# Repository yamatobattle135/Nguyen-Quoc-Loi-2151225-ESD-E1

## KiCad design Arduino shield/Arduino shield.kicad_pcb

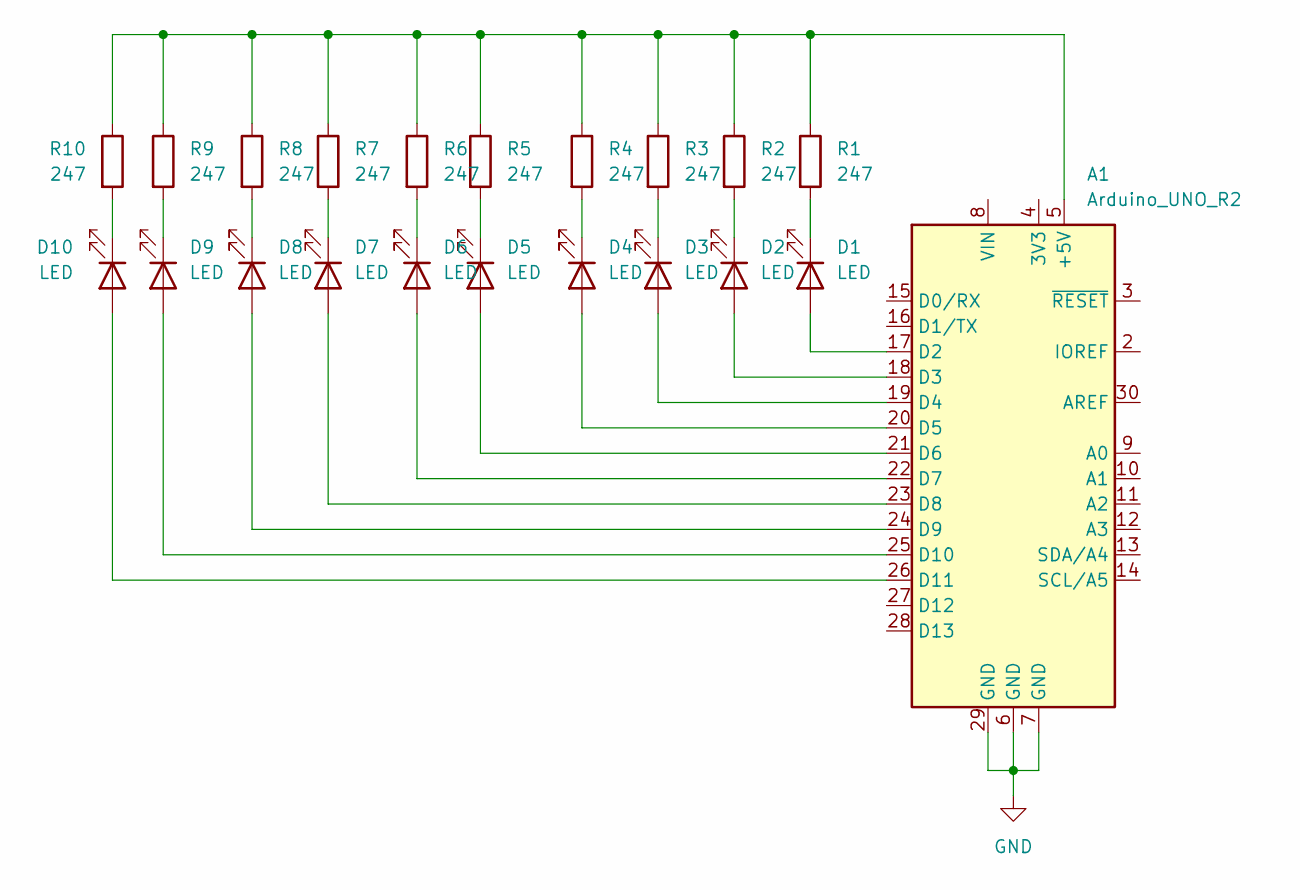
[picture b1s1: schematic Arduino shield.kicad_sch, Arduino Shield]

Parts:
A1: Arduino_UNO_R2
D1, D2, D3, D4, D5, D6, D7, D8, D9, D10: LED; LED_0805_2012Metric
R1, R2, R3, R4, R5, R6, R7, R8, R9, R10: 247; R_0805_2012Metric

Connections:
GND: A1.6 (GND), A1.7 (GND), A1.29 (GND)
unnamed: A1.5 (+5V), R1.1, R2.1, R3.1, R4.1, R5.1, R6.1, R7.1, R8.1, R9.1, R10.1
unnamed: A1.17 (D2), D1.2 (A)
unnamed: A1.18 (D3), D2.2 (A)
unnamed: A1.19 (D4), D3.2 (A)
unnamed: A1.20 (D5), D4.2 (A)
unnamed: A1.21 (D6), D5.2 (A)
unnamed: A1.22 (D7), D6.2 (A)
unnamed: A1.23 (D8), D7.2 (A)
unnamed: A1.24 (D9), D8.2 (A)
unnamed: A1.25 (D10), D9.2 (A)
unnamed: A1.26 (D11), D10.2 (A)
unnamed: D1.1 (K), R1.2
unnamed: D2.1 (K), R2.2
unnamed: D3.1 (K), R3.2
unnamed: D4.1 (K), R4.2
unnamed: D5.1 (K), R5.2
unnamed: D6.1 (K), R6.2
unnamed: D7.1 (K), R7.2
unnamed: D8.1 (K), R8.2
unnamed: D9.1 (K), R9.2
unnamed: D10.1 (K), R10.2

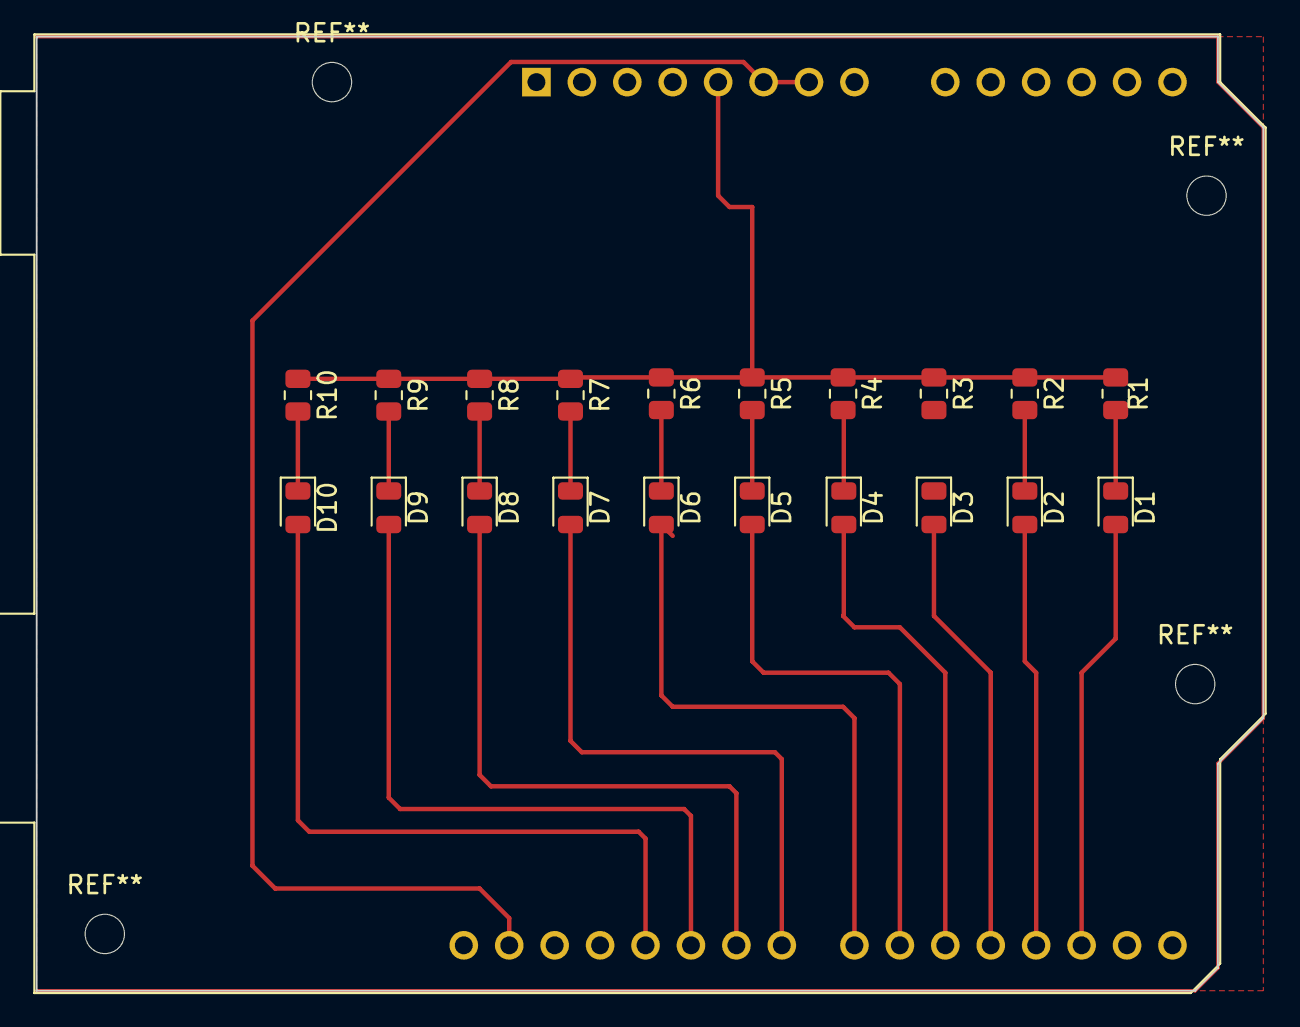
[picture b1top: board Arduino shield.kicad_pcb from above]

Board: 2 copper layers, 68.6 x 53.3 mm, 21 parts (0 on the bottom side), 22 nets.
